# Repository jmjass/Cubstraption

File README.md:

# Cubstraption
 Hybrid Box/GCC Controller for Super Smash Brothers

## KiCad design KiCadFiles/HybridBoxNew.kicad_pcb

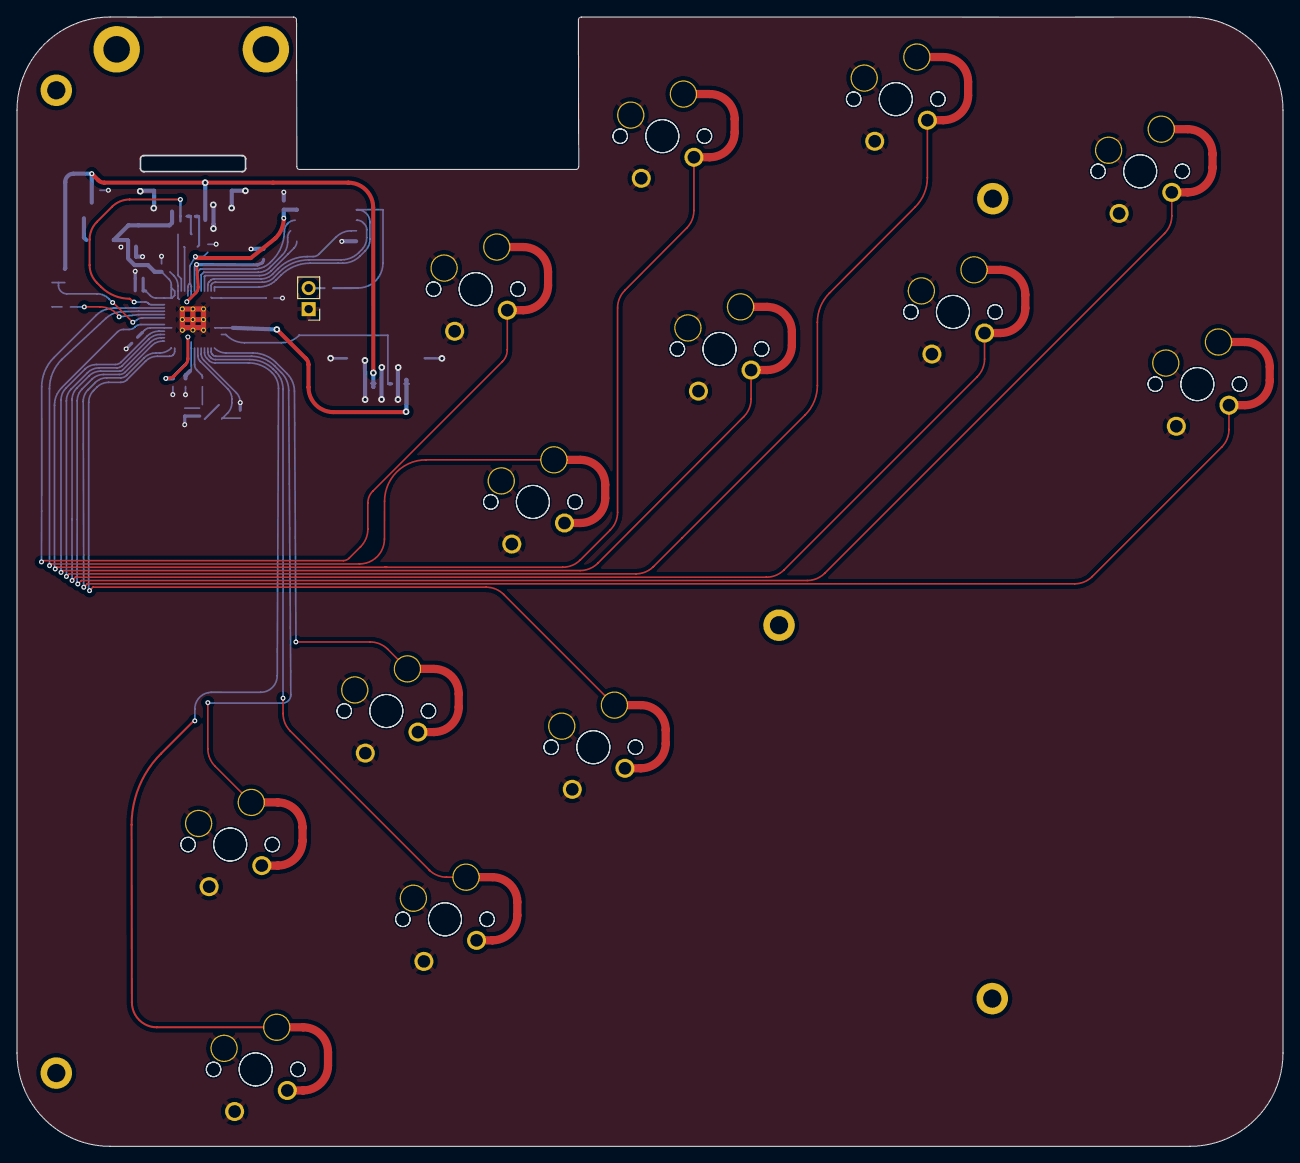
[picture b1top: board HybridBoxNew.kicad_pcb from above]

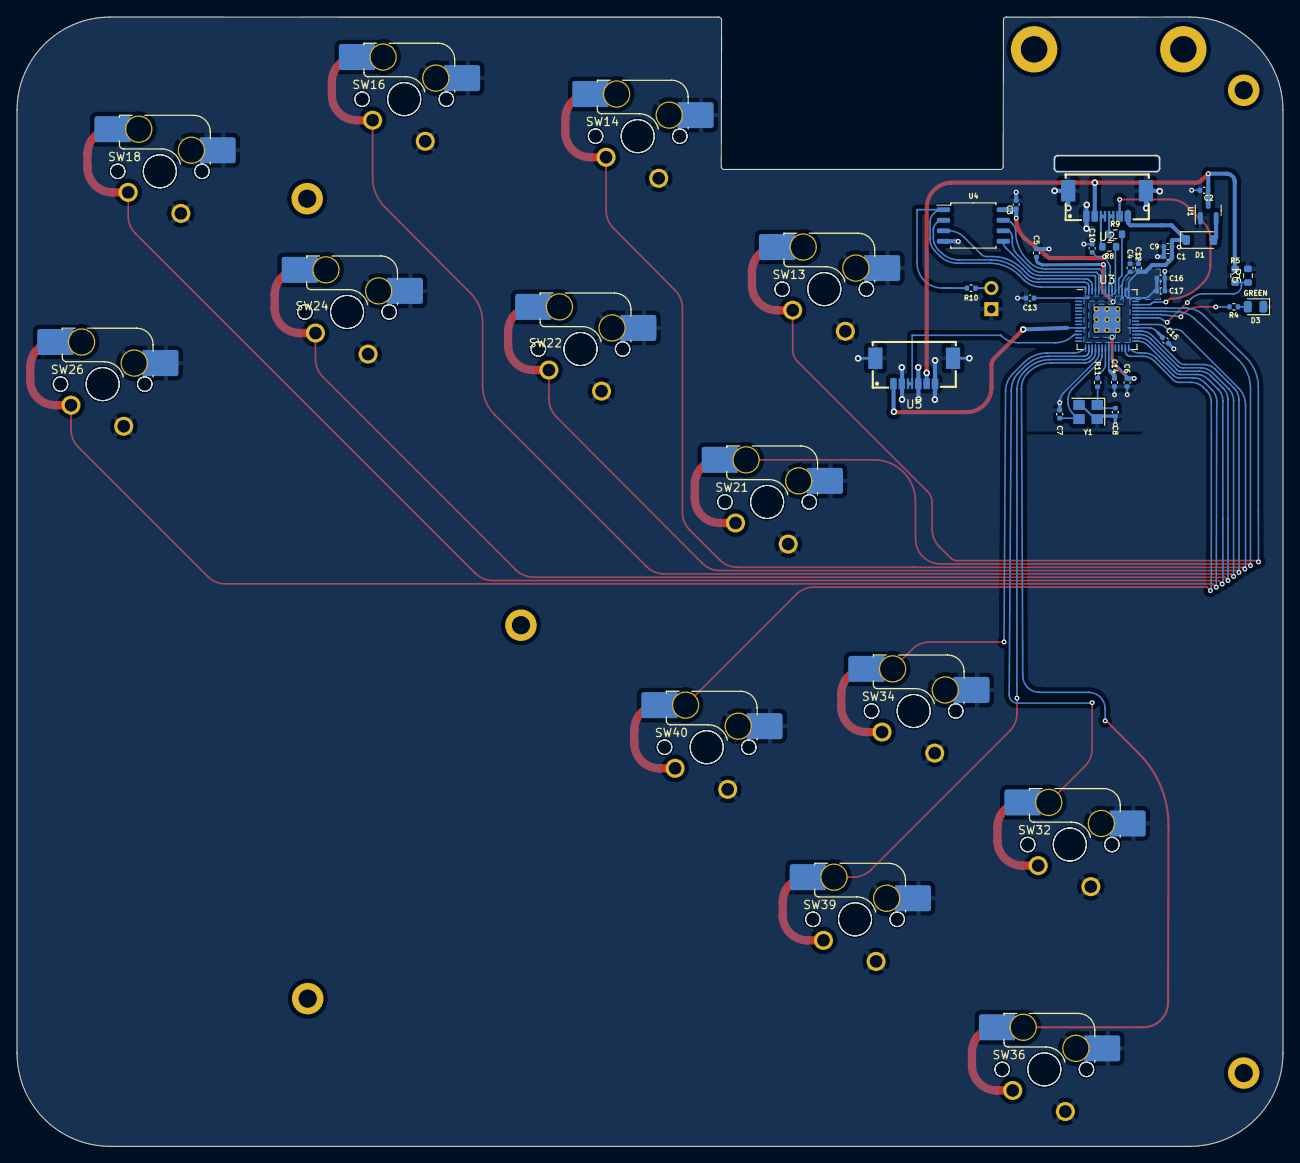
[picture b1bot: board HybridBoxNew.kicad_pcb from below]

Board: 2 copper layers, 152.7 x 136.2 mm, 63 parts (44 on the bottom side), 36 nets.

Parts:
C1, C2, C4, C10: 1uF; C_0402_1005Metric
C3, C5, C6, C12, C13, C14, C15, C16, C17: 100nF; C_0402_1005Metric
C7, C8: 22pF; C_0402_1005Metric
C9: 10uF; C_0402_1005Metric
D1: Schottky Diode; D_SOD-123
D3: GREEN; LED_0805_2012Metric
H5, H6, H7, H8, H8#2: MountingHole; MountingHole_2.2mm_M2_ISO14580_Pad
J1: Conn_01x02; PinHeader_1x02_P2.54mm_Vertical
R4: 470; R_0402_1005Metric
R5: 5.6k; R_0603_1608Metric
R6: 10k; R_0603_1608Metric
R8, R9: 27; R_0603_1608Metric
R10, R11: 1k; R_0402_1005Metric
SW12, SW15, SW17, SW19, SW20, SW23, SW25, SW27, SW33, SW35, SW37, SW38, SW41: MX_SW_solder; SW_MX_1u
SW13, SW14, SW16, SW18, SW21, SW22, SW24, SW26, SW32, SW34, SW36, SW39, SW40: MX_SW_HS; SW_MX_HS_1u
U1: XC6206; SOT-23
U2, U5: X05A26H12G; FPC-SMD_X05A26H12G
U3: RP2040; RP2040-QFN-56
U4: W25Q128JVS; SOIC-8_5.23x5.23mm_P1.27mm
Y1: 12MHz; Crystal_SMD_3225-4Pin_3.2x2.5mm

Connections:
+1V1: C4.1, C5.1, C6.1, U3.23 (DVDD), U3.45 (VREG_VOUT), U3.50 (DVDD)
+3V3: C1.2, C3.1, C9.1, C10.1, C12.1, C13.1, C14.1, C15.1, C16.1, C17.1, D1.1 (K), R10.2, U2.11, U2.12, U3.1 (IOVDD), U3.10 (IOVDD), U3.22 (IOVDD), U3.33 (IOVDD), U3.42 (IOVDD), U3.43 (ADC_AVDD), U3.44 (VREG_VIN), U3.48 (USB_VDD), U3.49 (IOVDD), U3.56 (QSPI_SS_N), U4.1 (~CS), U4.8 (VCC), U5.1, U5.2
+5V: C2.2, R5.1, U1.3 (VI), U2.3, U2.4, U5.9, U5.10
/D_+: R8.2, U3.47 (D+)
/D_-: R9.2, U3.46 (D-)
/XTAL_O: C8.2, R11.1, Y1.1
/~USB_BOOT: J1.2, R10.1
A: SW38.1, SW39.2, U3.17 (GPIO14)
B: SW20.1, SW21.2, U3.38 (GPIO26/ADC0)
C_DN: SW36.2, SW37.1, U3.18 (GPIO15)
C_LT: SW32.2, SW33.1, U3.16 (GPIO13)
C_RT: SW40.2, SW41.1, U3.27 (GPIO16)
C_UP: SW34.2, SW35.1, U3.15 (GPIO12)
D+: R8.1, U2.5, U2.6
D-: R9.1, U2.7, U2.8
DATA: U2.9, U2.10, U3.40 (GPIO28/ADC2)
GND: C1.1, C2.1, C3.2, C4.2, C5.2, C6.2, C7.1, C8.1, C9.2, C10.2, C12.2, C13.2, C14.2, C15.2, C16.2, C17.2, D3.1 (K), J1.1, R6.2, SW12.2, SW13.1, SW14.1, SW15.2, SW16.1, SW17.2, SW18.1, SW19.2, SW20.2, SW21.1, SW22.1, SW23.2, SW24.1, SW25.2, SW26.1, SW27.2, SW32.1, SW33.2, SW34.1, SW35.2, SW36.1, SW37.2, SW38.2, SW39.1, SW40.1, SW41.2, U1.1 (GND), U2.1, U2.2, U2.13, U2.14, U3.19 (TESTEN), U3.57 (GND), U4.4 (GND), U5.3, U5.4, U5.7, U5.8, U5.11, U5.12, U5.13, U5.14, Y1.2, Y1.4
GPIO9: U3.12 (GPIO9), U5.5, U5.6
LS: SW16.2, SW17.1, U3.31 (GPIO20)
MS: SW18.2, SW19.1, U3.29 (GPIO18)
unnamed: D1.2 (A), U1.2 (VO)
unnamed: D3.2 (A), R4.2
PICO_LED: R4.1, U3.37 (GPIO25)
QSPI_CLK: U3.52 (QSPI_SCLK), U4.6 (CLK)
R: SW12.1, SW13.2, U3.39 (GPIO27/ADC1)
SD0: U3.53 (QSPI_SD0), U4.5 (DI(IO0))
SD1: U3.55 (QSPI_SD1), U4.2 (DO(IO1))
SD2: U3.54 (QSPI_SD2), U4.3 (IO2)
SD3: U3.51 (QSPI_SD3), U4.7 (IO3)
UP: SW26.2, SW27.1, U3.28 (GPIO17)
VBUS_SENSE: R5.2, R6.1, U3.36 (GPIO24)
X: SW22.2, SW23.1, U3.32 (GPIO21)
XTAL_IN: C7.2, U3.20 (XTAL_IN), Y1.3
XTAL_OUT: R11.2, U3.21 (XTAL_OUT)
Y: SW14.2, SW15.1, U3.34 (GPIO22)
Z: SW24.2, SW25.1, U3.30 (GPIO19)

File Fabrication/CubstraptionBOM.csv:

Comment,Designator,Footprint,LCSC Part #
1uF,"C1,C2,C4,C10",Capacitor_SMD:C_0402_1005Metric,C52923
100nF,"C3,C5,C6,C12,C13,C14,C15,C16,C17",Capacitor_SMD:C_0402_1005Metric,C1525
10uF,C9,Capacitor_SMD:C_0402_1005Metric,C15525
22pF,"C7,C8",Capacitor_SMD:C_0402_1005Metric,C1555
D_Schottky,D1,qw-footprints:CUSTOM D_SOD-123,C8598
5.6k,R5,Resistor_SMD:R_0603_1608Metric,C23189
10k 0603,R6,Resistor_SMD:R_0603_1608Metric,C25804
10k 0402,R4,Resistor_SMD:R_0402_1005Metric,C25744
27,"R8,R9",Resistor_SMD:R_0603_1608Metric,C25190
1k,"R10,R11",Resistor_SMD:R_0402_1005Metric,C11702
,,,
XC6206,U1,Package_TO_SOT_SMD:SOT-23,C5446
RP2040,U3,qw-footprints:RP2040-QFN-56,C2040
W25Q128JVS,U4,Package_SO:SOIC-8_5.23x5.23mm_P1.27mm,C97521
12MHz,Y1,Crystal:Crystal_SMD_3225-4Pin_3.2x2.5mm,C9002
PICO_LED,D3,LED_SMD:LED_0805_2012Metric,C34499
MX_SW_HS,"SW13, SW14, SW16, SW18, SW21, SW22, SW24, SW26, SW32, SW34, SW36, SW39, SW40",SW_MX_HS_1u,C5156480
X05A26H12G,"U2, U5",FPC-SMD_X05A26H12G,C519263

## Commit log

2024-04-04 init commit
2024-04-04 added 3d print port
2025-06-06 Pushed new design
2025-11-19 3DP Mid Case
